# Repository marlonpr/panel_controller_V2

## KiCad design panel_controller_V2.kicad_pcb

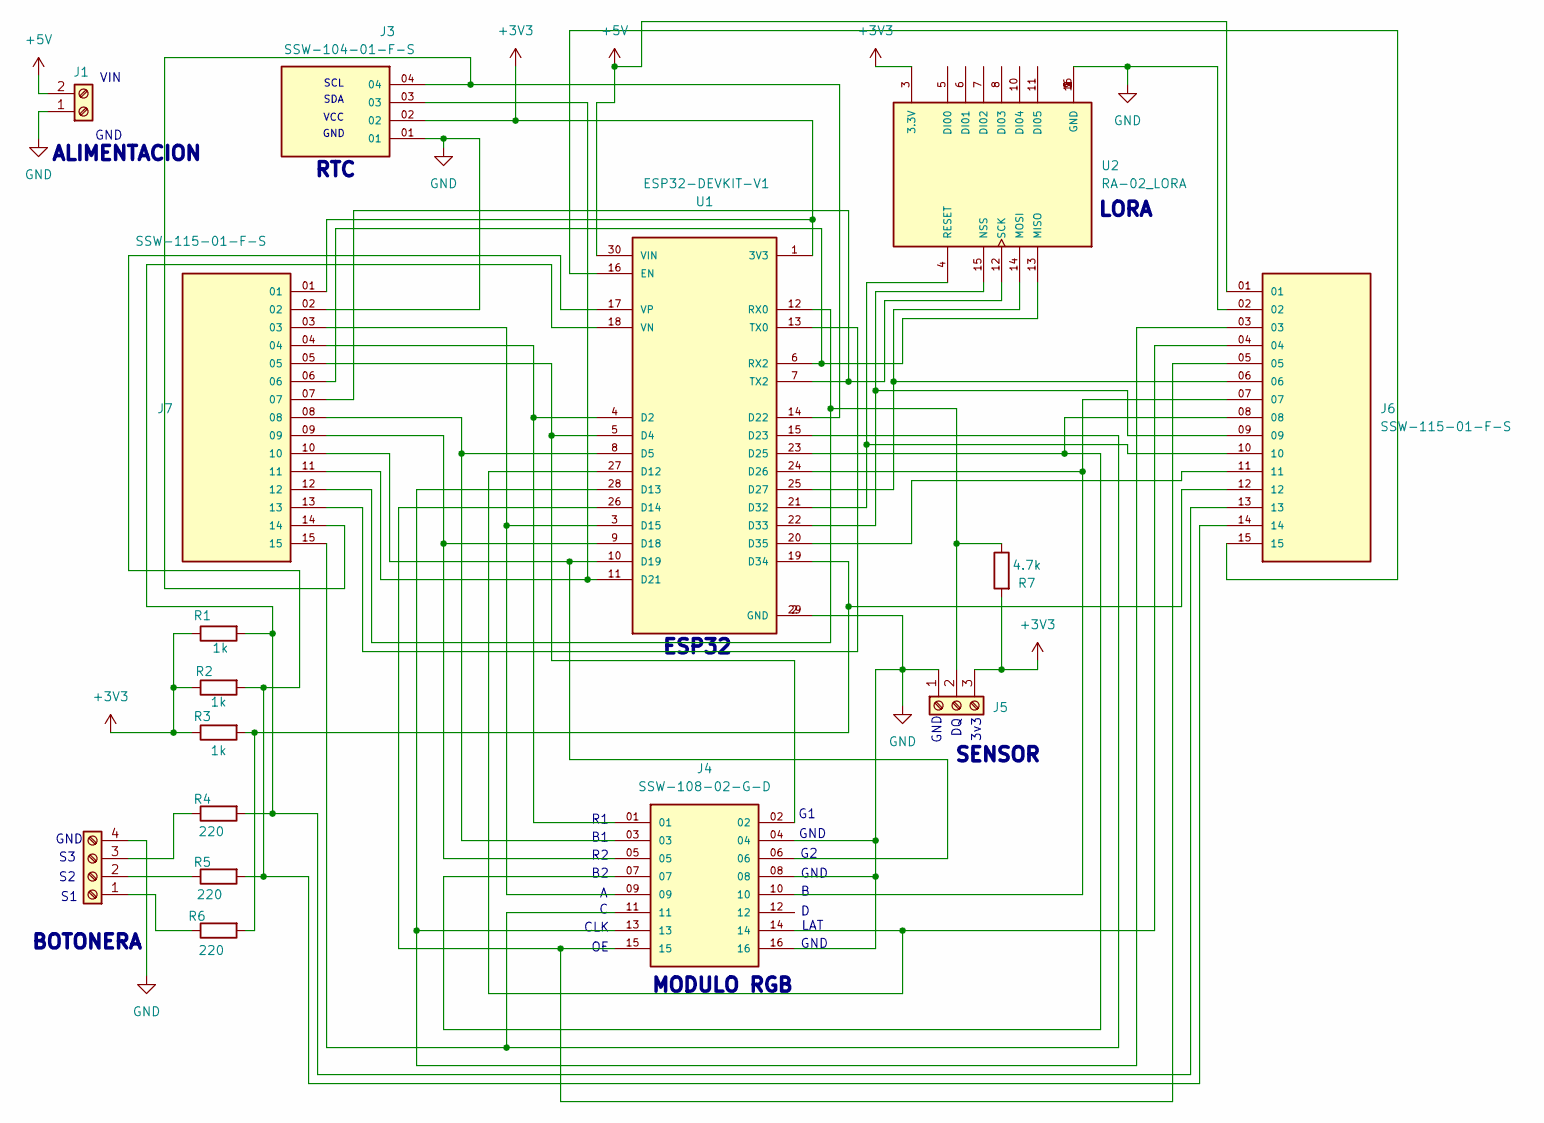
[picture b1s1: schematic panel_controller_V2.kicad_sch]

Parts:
J1: Screw_Terminal_01x02; TerminalBlock_Altech_AK300-2_P5.00mm
J2: Screw_Terminal_01x04; TerminalBlock_Altech_AK300-4_P5.00mm
J3: SSW-104-01-F-S; SAMTEC_SSW-104-01-F-S-RTC; PARTREV R
J4: SSW-108-02-G-D; SAMTEC_SSW-108-02-G-D
J5: Screw_Terminal_01x03; TerminalBlock_Altech_AK300-3_P5.00mm
J6, J7: SSW-115-01-F-S; SAMTEC_SSW-115-01-F-S; PARTREV R
R1, R2, R3: 1k; R_Axial_DIN0207_L6.3mm_D2.5mm_P7.62mm_Horizontal
R4, R5, R6: 220; R_Axial_DIN0207_L6.3mm_D2.5mm_P7.62mm_Horizontal
R7: 4.7k; R_Axial_DIN0207_L6.3mm_D2.5mm_P7.62mm_Horizontal
U1: ESP32-DEVKIT-V1; MODULE_ESP32_DEVKIT_V1; PARTREV N/A
U2: RA-02_LORA; TE_826629-8x2

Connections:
+3V3: J3.02, J5.3, J7.01, R1.1, R2.1, R3.1, R7.2, U1.1 (3V3), U2.3 (3.3V)
+5V: J1.2, J6.01, U1.30 (VIN)
GND: J1.1, J2.4, J3.01, J4.04, J4.08, J4.16, J5.1, J6.02, J7.02, U1.2 (GND), U1.29 (GND), U2.1 (GND), U2.2 (GND), U2.9 (GND), U2.16 (GND)
unnamed: J2.1, R6.1
unnamed: J2.2, R5.1
unnamed: J2.3, R4.1
unnamed: J5.2, J7.12, R7.1, U1.12 (RX0)
unnamed: J4.01, J7.04, U1.4 (D2)
unnamed: J4.02, J7.05, U1.5 (D4)
unnamed: J4.03, J7.08, U1.8 (D5)
unnamed: J4.14, J6.04, U1.27 (D12)
unnamed: J4.13, J6.03, U1.28 (D13)
unnamed: J4.15, J6.05, U1.26 (D14)
unnamed: J4.09, J7.03, U1.3 (D15)
unnamed: J4.05, J7.09, U1.9 (D18)
unnamed: J4.06, J7.10, U1.10 (D19)
unnamed: J3.03, J7.11, U1.11 (D21)
unnamed: J3.04, J7.14, U1.14 (D22)
unnamed: J4.11, J7.15, U1.15 (D23)
unnamed: J4.07, J6.08, U1.23 (D25)
unnamed: J4.10, J6.07, U1.24 (D26)
unnamed: J6.06, U1.25 (D27), U2.14 (MOSI)
unnamed: J6.10, U1.21 (D32), U2.4 (RESET)
unnamed: J6.09, U1.22 (D33), U2.15 (NSS)
unnamed: J6.12, R3.2, R6.2, U1.19 (D34)
unnamed: J6.11, U1.20 (D35)
unnamed: J6.15, U1.16 (EN)
unnamed: J7.06, U1.6 (RX2), U2.13 (MISO)
unnamed: J7.13, U1.13 (TX0)
unnamed: J7.07, U1.7 (TX2), U2.12 (SCK)
unnamed: J6.13, R1.2, R4.2, U1.18 (VN)
unnamed: J6.14, R2.2, R5.2, U1.17 (VP)

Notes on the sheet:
ALIMENTACION
ESP32
GND
LORA
MODULO RGB
BOTONERA
CLK
SCL
LAT
VCC
3v3
SDA
VIN
RTC
SENSOR

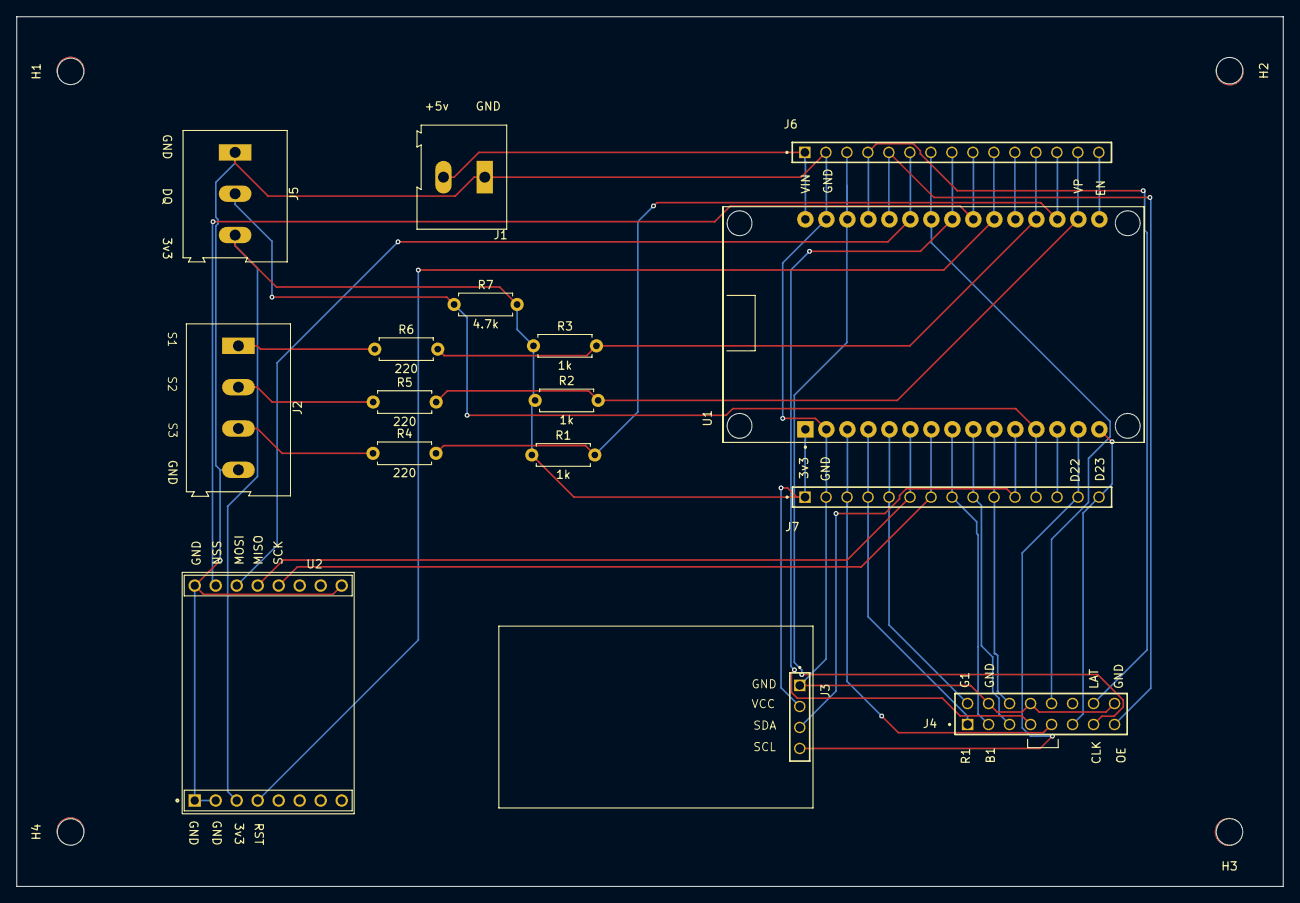
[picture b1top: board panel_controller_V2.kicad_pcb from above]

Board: 2 copper layers, 153.2 x 105.2 mm, 20 parts (0 on the bottom side), 32 nets.

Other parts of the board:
H1, H2, H3, H4: 3.2mm_M3_NR

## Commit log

2026-04-14 v1 ok
2026-04-15 headers parallel to esp32 added
2026-04-28 Ignore .history and DS_Store, cleanup project
2026-04-30 Removed copper ring on NPTH and clean
2026-05-20 3d models path update
